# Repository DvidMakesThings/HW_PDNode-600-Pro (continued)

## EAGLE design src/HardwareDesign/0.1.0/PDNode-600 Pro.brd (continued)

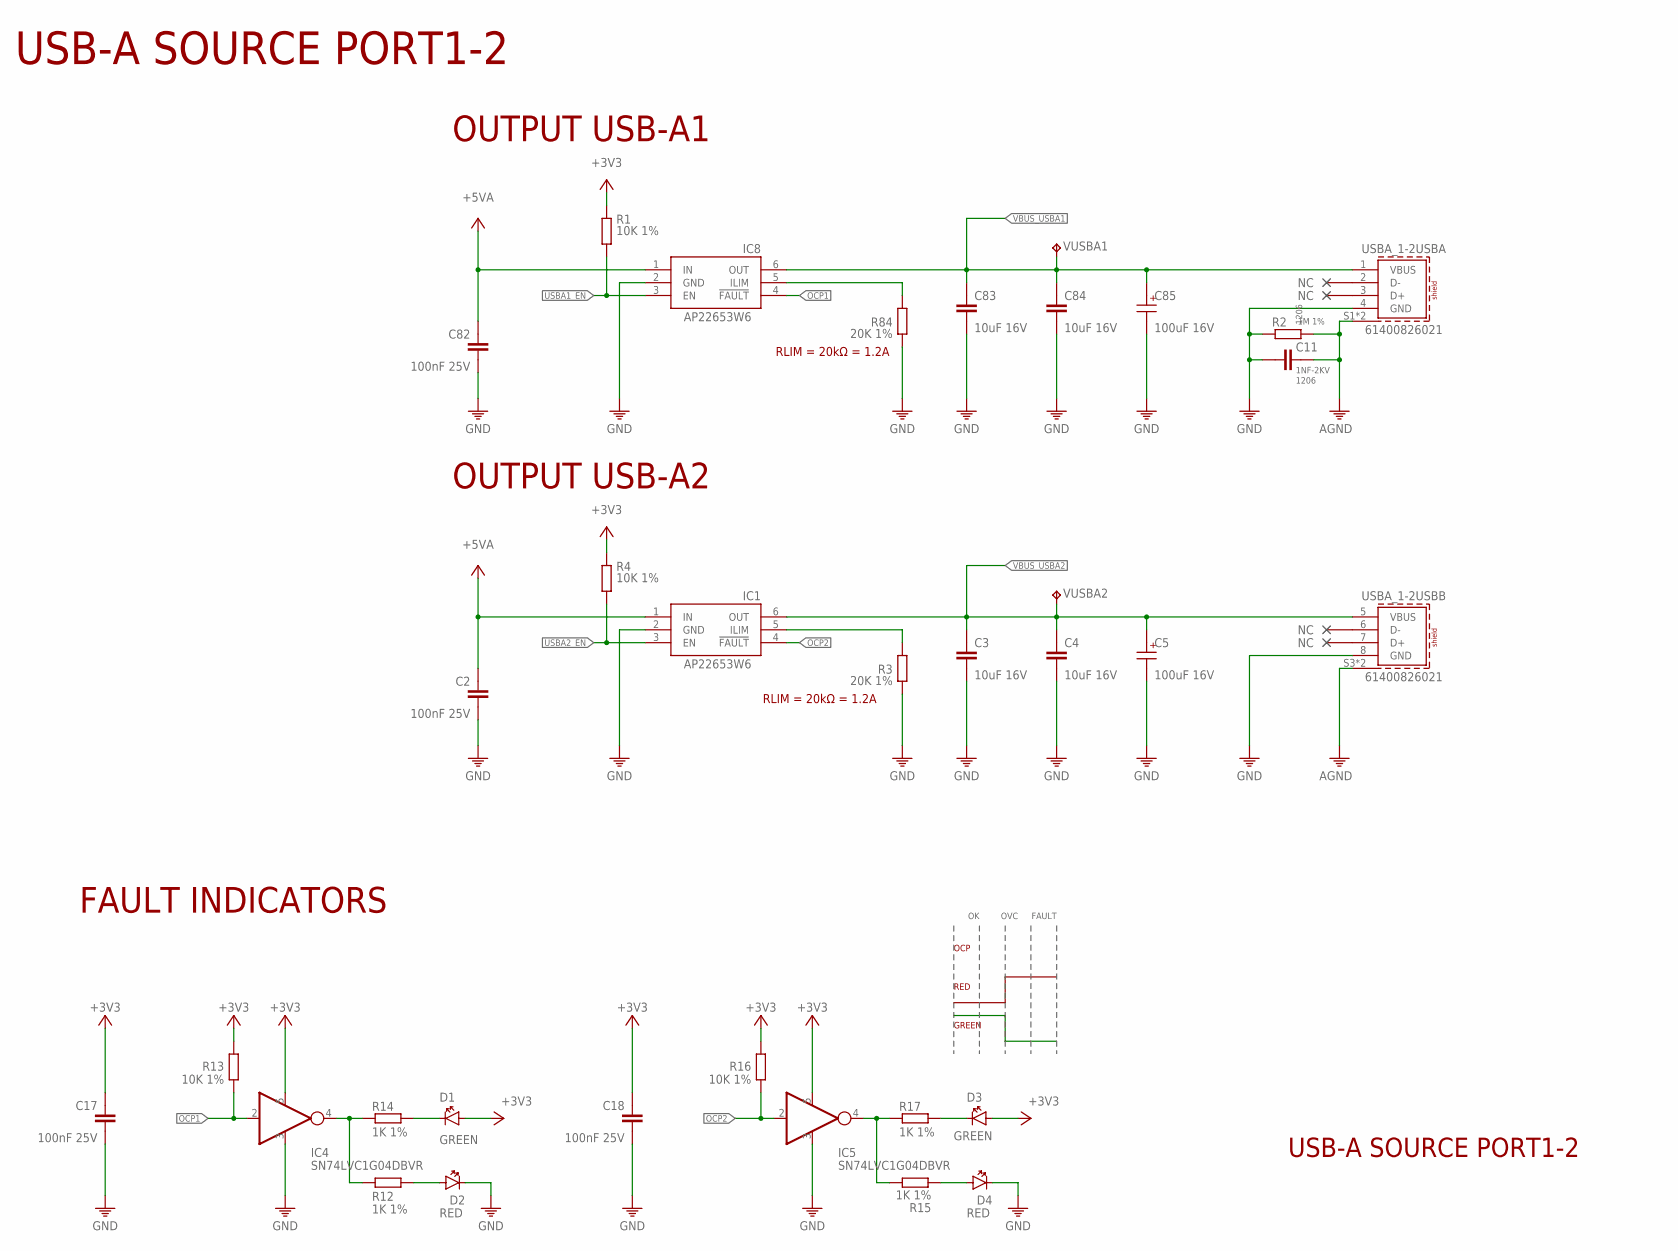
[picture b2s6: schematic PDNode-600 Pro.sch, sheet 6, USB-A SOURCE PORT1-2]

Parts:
C2, C17, C18, C82: 100nF 25V; 0201
C3, C4, C83, C84: 10uF 16V; 0603
C5, C85: 100uF 16V; 5X5.5(DXL)
C11: 1NF-2KV; 1206
D1, D3: GREEN; LEDC1608X35N_FLAT-G
D2, D4: RED; LEDC1608X35N_FLAT-R
IC1, IC8: AP22653W6; SOT23-6
IC4, IC5: SN74LVC1G04DBVR; SOT95P280X145-5N
R1, R4, R13, R16: 10K 1%; 0402
R2: 1M 1%; 1206
R3, R84: 20K 1%; 0201
R12, R14, R15, R17: 1K 1%; 0402
USBA_1-2: 61400826021
VUSBA1, VUSBA2: TPB1,27; B1,27

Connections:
+3V3: C17.1, C18.1, D1.A, D3.A, IC4.5 (V+), IC5.5 (V+), R1.1, R4.1, R13.2, R16.2; also elsewhere on the board
+5VA: C2.1, C82.1, IC1.1 (IN), IC8.1 (IN); also elsewhere on the board
AGND: C11.1, R2.2, USBA_1-2.S1 (SHIELD), USBA_1-2.S2 (SHIELD), USBA_1-2.S3 (SHIELD), USBA_1-2.S4 (SHIELD); also elsewhere on the board
GND: C2.2, C3.2, C4.2, C5.2 (-), C11.2, C17.2, C18.2, C82.2, C83.2, C84.2, C85.2 (-), D2.C, D4.C, IC1.2 (GND), IC4.3 (V-), IC5.3 (V-), IC8.2 (GND), R2.1, R3.2, R84.2, USBA_1-2.4 (GND), USBA_1-2.8 (GND); also elsewhere on the board
unnamed: IC1.5 (ILIM), R3.1
unnamed: D2.A, R12.2
unnamed: IC4.4 (OUT), R12.1, R14.1
unnamed: D1.C, R14.2
unnamed: D4.A, R15.1
unnamed: IC5.4 (OUT), R15.2, R17.1
unnamed: D3.C, R17.2
unnamed: IC8.5 (ILIM), R84.1
OCP1: IC4.2 (IN), IC8.4 (!FAULT), R13.1; also elsewhere on the board
OCP2: IC1.4 (!FAULT), IC5.2 (IN), R16.1; also elsewhere on the board
USBA1_EN: IC8.3 (EN), R1.2; also elsewhere on the board
USBA2_EN: IC1.3 (EN), R4.2; also elsewhere on the board
VBUS_USBA1: C83.1, C84.1, C85.1 (+), IC8.6 (OUT), USBA_1-2.1 (VBUS), VUSBA1.TP
VBUS_USBA2: C3.1, C4.1, C5.1 (+), IC1.6 (OUT), USBA_1-2.5 (VBUS), VUSBA2.TP

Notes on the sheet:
OUTPUT USB-A1
RLIM = 20kΩ = 1.2A
OUTPUT USB-A2
FAULT INDICATORS
USB-A SOURCE PORT1-2
OCP
RED
GREEN
OVC
FAULT

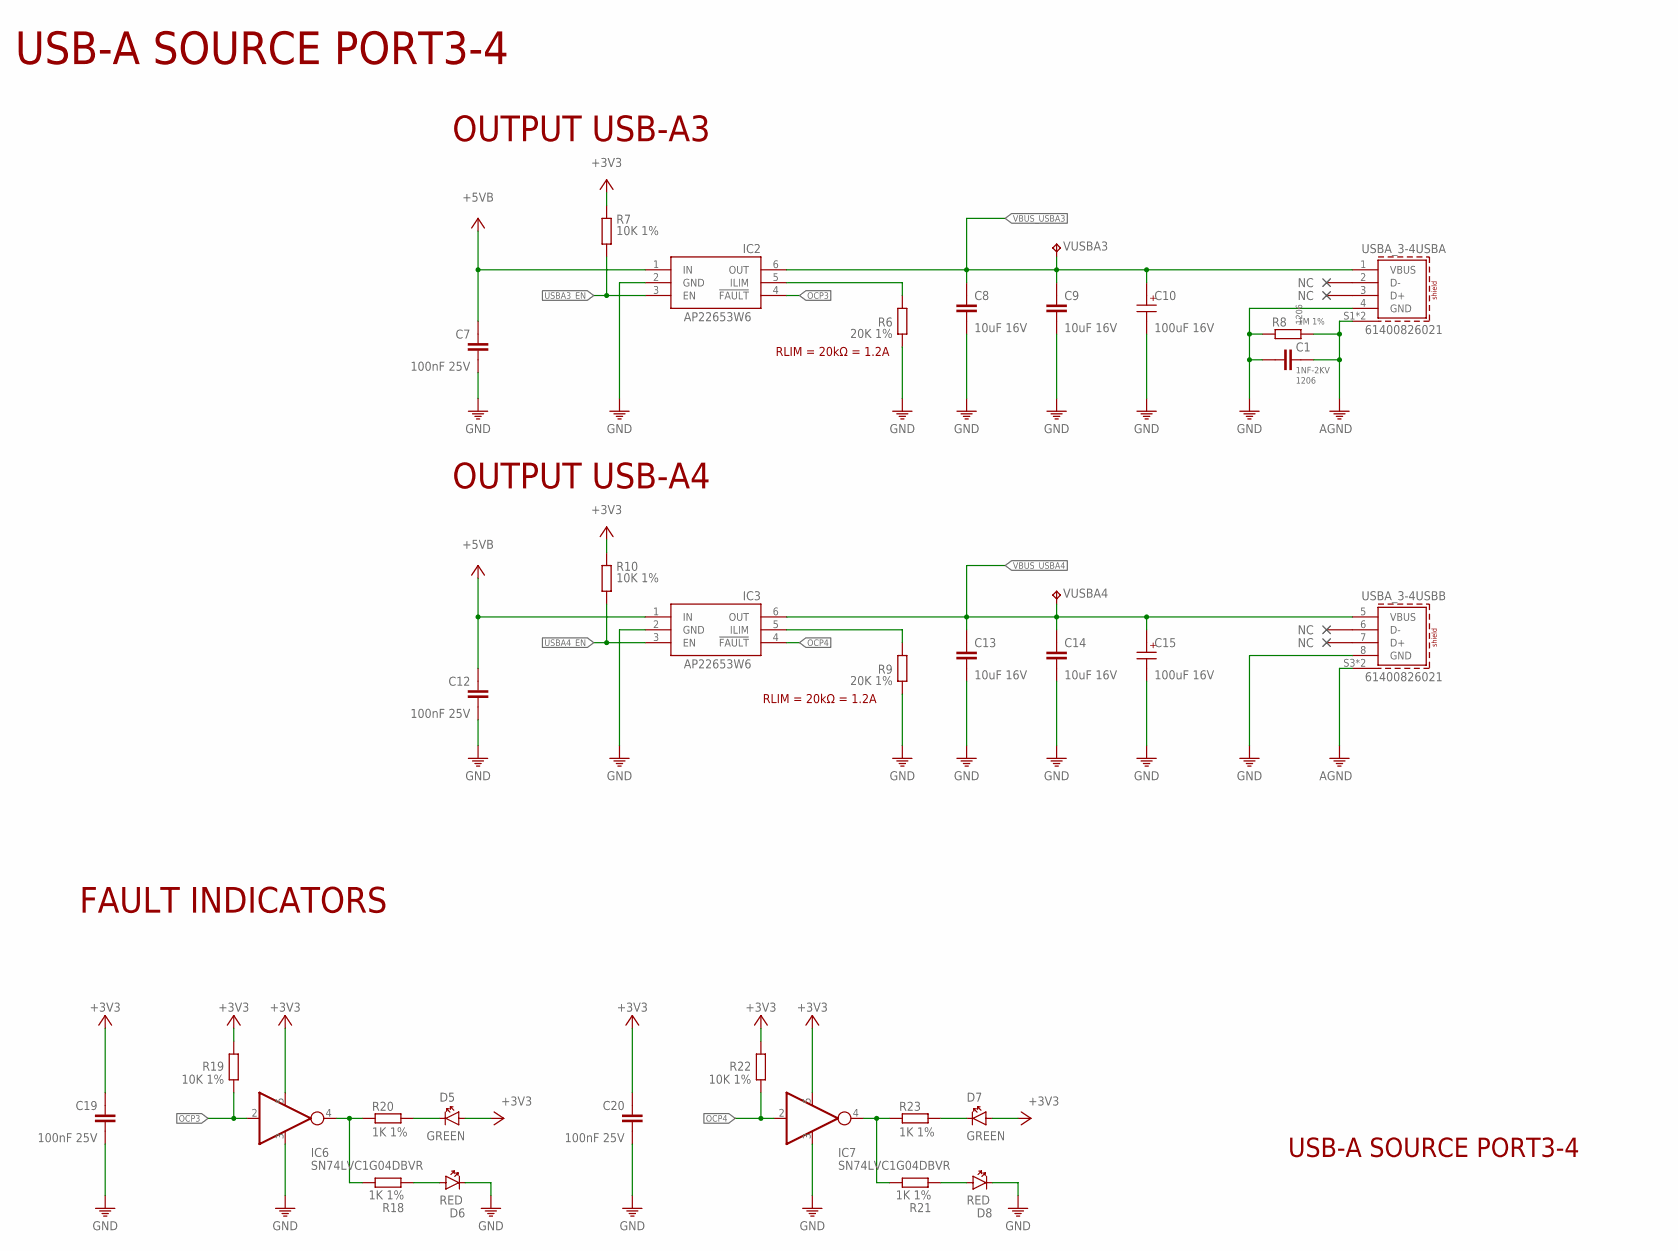
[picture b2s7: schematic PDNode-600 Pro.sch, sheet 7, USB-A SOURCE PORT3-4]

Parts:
C1: 1NF-2KV; 1206
C7, C12, C19, C20: 100nF 25V; 0201
C8, C9, C13, C14: 10uF 16V; 0603
C10, C15: 100uF 16V; 5X5.5(DXL)
D5, D7: GREEN; LEDC1608X35N_FLAT-G
D6, D8: RED; LEDC1608X35N_FLAT-R
IC2, IC3: AP22653W6; SOT23-6
IC6, IC7: SN74LVC1G04DBVR; SOT95P280X145-5N
R6, R9: 20K 1%; 0201
R7, R10, R19, R22: 10K 1%; 0402
R8: 1M 1%; 1206
R18, R20, R21, R23: 1K 1%; 0402
USBA_3-4: 61400826021
VUSBA3, VUSBA4: TPB1,27; B1,27

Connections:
+3V3: C19.1, C20.1, D5.A, D7.A, IC6.5 (V+), IC7.5 (V+), R7.1, R10.1, R19.2, R22.2; also elsewhere on the board
+5VB: C7.1, C12.1, IC2.1 (IN), IC3.1 (IN); also elsewhere on the board
AGND: C1.1, R8.2, USBA_3-4.S1 (SHIELD), USBA_3-4.S2 (SHIELD), USBA_3-4.S3 (SHIELD), USBA_3-4.S4 (SHIELD); also elsewhere on the board
GND: C1.2, C7.2, C8.2, C9.2, C10.2 (-), C12.2, C13.2, C14.2, C15.2 (-), C19.2, C20.2, D6.C, D8.C, IC2.2 (GND), IC3.2 (GND), IC6.3 (V-), IC7.3 (V-), R6.2, R8.1, R9.2, USBA_3-4.4 (GND), USBA_3-4.8 (GND); also elsewhere on the board
unnamed: IC2.5 (ILIM), R6.1
unnamed: IC3.5 (ILIM), R9.1
unnamed: D6.A, R18.1
unnamed: IC6.4 (OUT), R18.2, R20.1
unnamed: D5.C, R20.2
unnamed: D8.A, R21.1
unnamed: IC7.4 (OUT), R21.2, R23.1
unnamed: D7.C, R23.2
OCP3: IC2.4 (!FAULT), IC6.2 (IN), R19.1; also elsewhere on the board
OCP4: IC3.4 (!FAULT), IC7.2 (IN), R22.1; also elsewhere on the board
USBA3_EN: IC2.3 (EN), R7.2; also elsewhere on the board
USBA4_EN: IC3.3 (EN), R10.2; also elsewhere on the board
VBUS_USBA3: C8.1, C9.1, C10.1 (+), IC2.6 (OUT), USBA_3-4.1 (VBUS), VUSBA3.TP
VBUS_USBA4: C13.1, C14.1, C15.1 (+), IC3.6 (OUT), USBA_3-4.5 (VBUS), VUSBA4.TP

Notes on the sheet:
OUTPUT USB-A3
RLIM = 20kΩ = 1.2A
OUTPUT USB-A4
USB-A SOURCE PORT3-4
FAULT INDICATORS

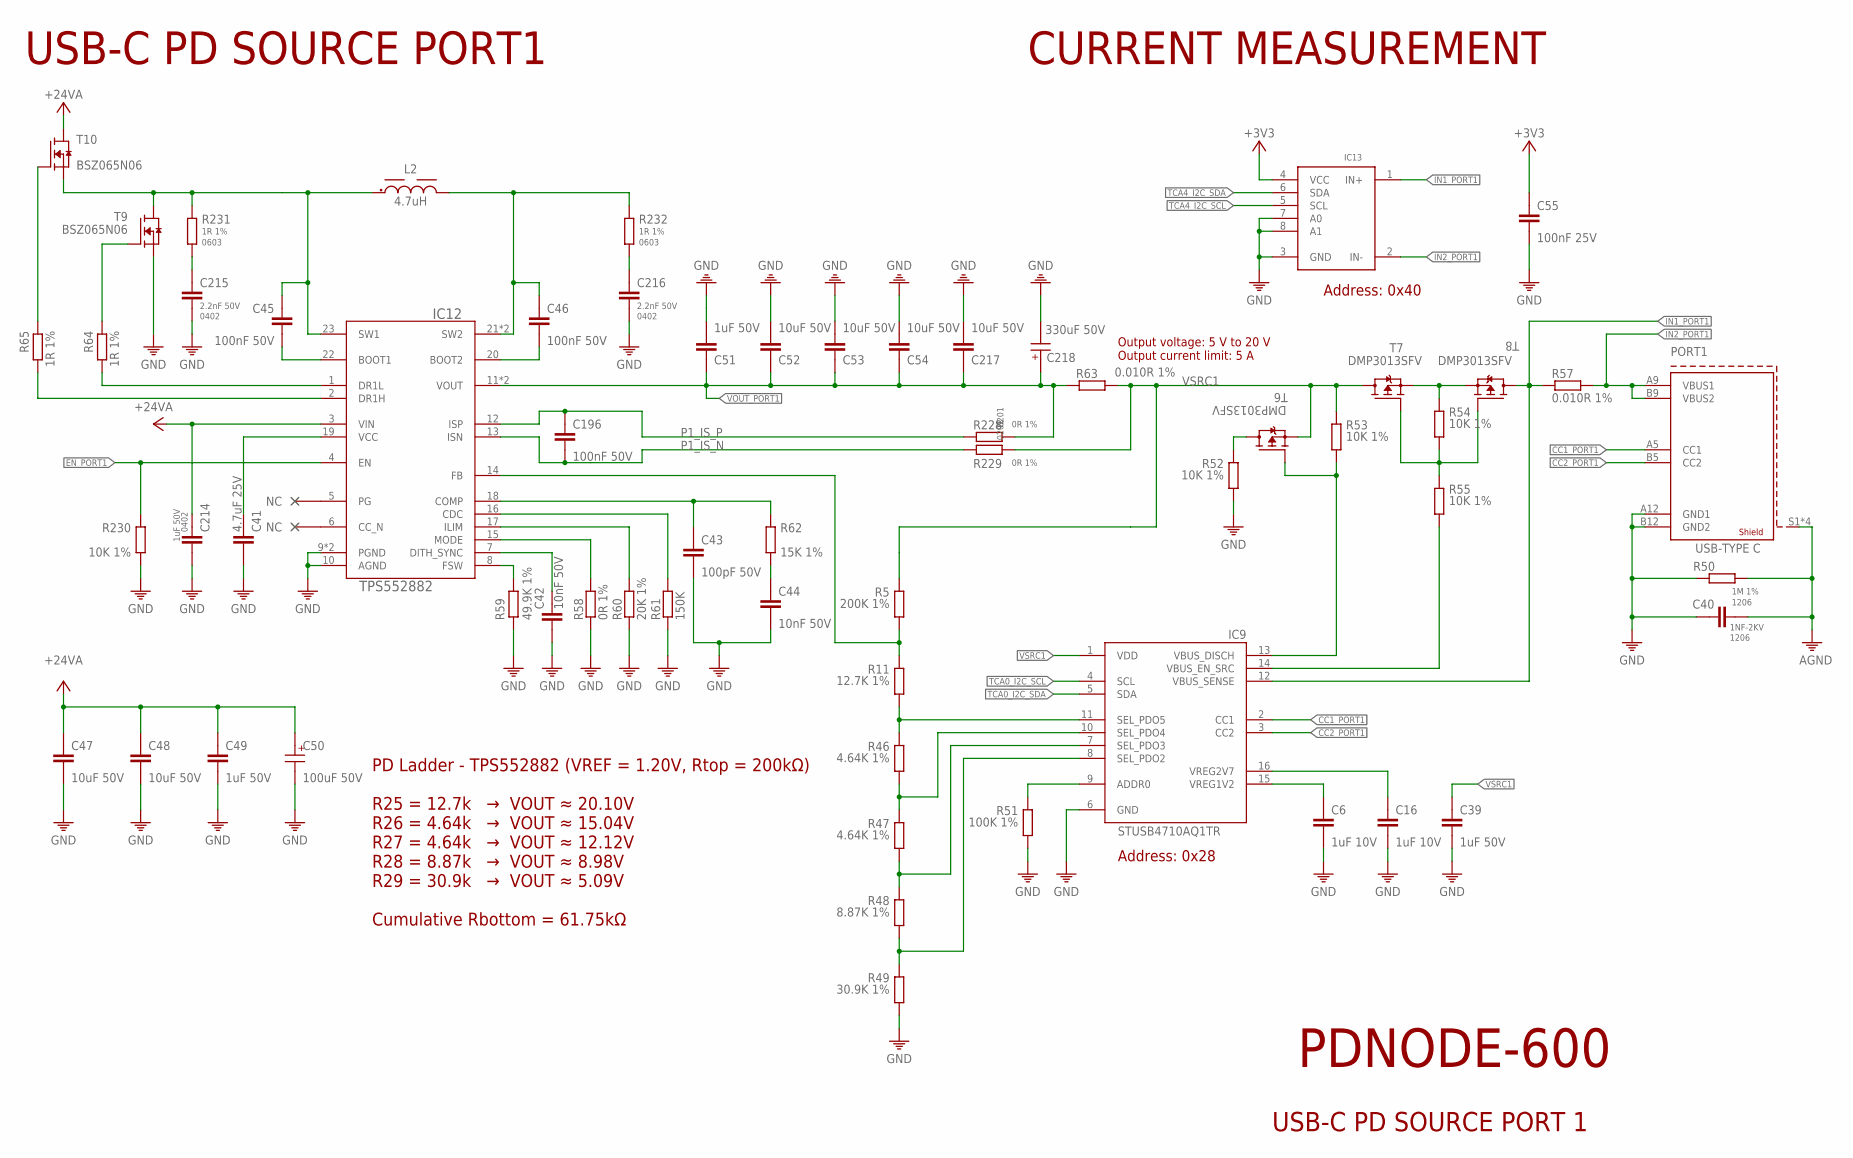
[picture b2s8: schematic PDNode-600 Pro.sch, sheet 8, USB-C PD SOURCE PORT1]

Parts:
C6, C16: 1uF 10V; 0201
C39: 1uF 50V; 0603
C40: 1NF-2KV; 1206
C41: 4.7uF 25V; 0402
C42, C44: 10nF 50V; 0201
C43: 100pF 50V; 0402
C45, C46, C196: 100nF 50V; 0402
C47, C48, C52, C53, C54, C217: 10uF 50V; 0805
C49: 1uF 50V; 0805
C50: 100uF 50V; 6.3X7.7(DXL)
C51, C214: 1uF 50V; 0402
C55: 100nF 25V; 0201
C215, C216: 2.2nF 50V; 0402
C218: 330uF 50V; 10X10.5(DXL)
IC9: STUSB4710AQ1TR; QFN50P300X300X55-16N
IC12: TPS552882; RPM0026A-MFG
IC13: INA219BIDCNT; SOT23-8
L2: 4.7uH; WE-PD_1280
PORT1: 632722100213
R5: 200K 1%; 0201
R11: 12.7K 1%; 0201
R46, R47: 4.64K 1%; 0201
R48: 8.87K 1%; 0201
R49: 30.9K 1%; 0201
R50: 1M 1%; 1206
R51: 100K 1%; 0201
R52, R53, R55: 10K 1%; 0402
R54, R230: 10K 1%; 0201
R57, R63: 0.010R 1%; 2512
R58, R228, R229: 0R 1%; 0201
R59: 49.9K 1%; 0201
R60: 20K 1%; 0201
R61: 150K; R0201
R62: 15K 1%; 0201
R64, R65: 1R 1%; 0402
R231, R232: 1R 1%; 0603
T6, T7, T8: DMP3013SFV; POWERDI3333-8_UX_DIO-L
T9, T10: BSZ065N06; POWERDI3333-8_UX_DIO-L

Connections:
+3V3: C55.1, IC13.4 (VCC); also elsewhere on the board
+24V_A: C47.1, C48.1, C49.1, C50.1 (+), C214.1, IC12.3 (VIN), T10.5 (D), T10.6 (D), T10.7 (D), T10.8 (D), T10.9 (D); also elsewhere on the board
AGND: C40.2, PORT1.S1 (SHIELD1), PORT1.S2 (SHIELD1), PORT1.S3 (SHIELD1), PORT1.S4 (SHIELD1), R50.2; also elsewhere on the board
CC1_PORT1: IC9.2 (CC1), PORT1.A5 (CC1)
CC2_PORT1: IC9.3 (CC2), PORT1.B5 (CC2)
EN_PORT1: IC12.4 (EN), R230.1; also elsewhere on the board
GND: C6.2, C16.2, C39.2, C40.1, C41.2, C42.2, C43.2, C44.2, C47.2, C48.2, C49.2, C50.2 (-), C51.2, C52.2, C53.2, C54.2, C55.2, C214.2, C215.2, C216.2, C217.2, C218.2 (-), IC9.6 (GND), IC12.9 (PGND), IC12.10 (AGND), IC12.24 (PGND), IC13.3 (GND), IC13.7 (A0), IC13.8 (A1), PORT1.A12 (GND1), PORT1.B12 (GND2), R49.2, R50.1, R51.2, R52.2, R58.2, R59.2, R60.2, R61.2, R230.2, T9.1 (S), T9.2 (S), T9.3 (S); also elsewhere on the board
IN1_PORT1: IC9.12 (VBUS_SENSE), IC13.1 (IN+), R57.1, T8.5 (D), T8.6 (D), T8.7 (D), T8.8 (D), T8.9 (D)
IN2_PORT1: IC13.2 (IN-), PORT1.A9 (VBUS1), PORT1.B9 (VBUS2), R57.2
unnamed: IC12.14 (FB), R5.2, R11.1
unnamed: C215.1, R231.2
unnamed: C216.1, R232.2
unnamed: IC9.11 (SEL_PDO5), R11.2, R46.1
unnamed: IC9.10 (SEL_PDO4), R46.2, R47.1
unnamed: IC9.7 (SEL_PDO3), R47.2, R48.1
unnamed: IC9.8 (SEL_PDO2), R48.2, R49.1
unnamed: C6.1, IC9.15 (VREG1V2)
unnamed: C16.1, IC9.16 (VREG2V7)
unnamed: IC9.9 (ADDR0), R51.1
unnamed: R52.1, T6.5 (D), T6.6 (D), T6.7 (D), T6.8 (D), T6.9 (D)
unnamed: IC9.13 (VBUS_DISCH), R53.2, T6.4 (G)
unnamed: R54.1, T7.1 (S), T7.2 (S), T7.3 (S), T8.1 (S), T8.2 (S), T8.3 (S)
unnamed: R54.2, R55.1, T7.4 (G), T8.4 (G)
unnamed: IC9.14 (VBUS_EN_SRC), R55.2
unnamed: C44.1, R62.2
unnamed: IC12.8 (FSW), R59.1
unnamed: C42.1, IC12.7 (DITH_SYNC)
unnamed: IC12.15 (MODE), R58.1
unnamed: IC12.17 (ILIM), R60.1
unnamed: IC12.16 (CDC), R61.1
unnamed: C43.1, IC12.18 (COMP), R62.1
unnamed: C41.1, IC12.19 (VCC)
unnamed: C45.1, IC12.23 (SW1), L2.1, R231.1, T9.5 (D), T9.6 (D), T9.7 (D), T9.8 (D), T9.9 (D), T10.1 (S), T10.2 (S), T10.3 (S)
unnamed: C46.1, IC12.21 (SW2), IC12.25 (SW2), L2.2, R232.1
unnamed: C45.2, IC12.22 (BOOT1)
unnamed: C46.2, IC12.20 (BOOT2)
unnamed: R65.2, T10.4 (G)
unnamed: R64.2, T9.4 (G)
unnamed: IC12.1 (DR1L), R64.1
unnamed: IC12.2 (DR1H), R65.1
P1_IS_N: C196.2, IC12.13 (ISN), R229.1
P1_IS_P: C196.1, IC12.12 (ISP), R228.1
TCA0_I2C_SCL: IC9.4 (SCL); also elsewhere on the board
TCA0_I2C_SDA: IC9.5 (SDA); also elsewhere on the board
TCA4_I2C_SCL: IC13.5 (SCL); also elsewhere on the board
TCA4_I2C_SDA: IC13.6 (SDA); also elsewhere on the board
VOUT_PORT1: C51.1, C52.1, C53.1, C54.1, C217.1, C218.1 (+), IC12.11 (VOUT), IC12.26 (VOUT), R63.1, R228.2
VSRC1: C39.1, IC9.1 (VDD), R5.1, R53.1, R63.2, R229.2, T6.1 (S), T6.2 (S), T6.3 (S), T7.5 (D), T7.6 (D), T7.7 (D), T7.8 (D), T7.9 (D)

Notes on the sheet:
USB-C PD SOURCE PORT1
CURRENT MEASUREMENT
Output voltage: 5 V to 20 V Output current limit: 5 A
PD Ladder - TPS552882 (VREF = 1.20V, Rtop = 200kΩ) R25 = 12.7k → VOUT ≈ 20.10V R26 = 4.64k → VOUT ≈ 15.04V R27 = 4.64k → VOUT ≈ 12.12V R28 = 8.87k → VOUT ≈ 8.98V R29 = 30.9k → VOUT ≈ 5.09V Cumulative Rbottom = 61.75kΩ
Address: 0x40
Address: 0x28
USB-C PD SOURCE PORT 1
PDNODE-600

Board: 4 copper layers, 285 parts (8 on the bottom side), 167 nets, no tracks yet.

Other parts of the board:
U$1: ROHS_LOGO_0.18_IN
U$2: OSHW-LOGO-L

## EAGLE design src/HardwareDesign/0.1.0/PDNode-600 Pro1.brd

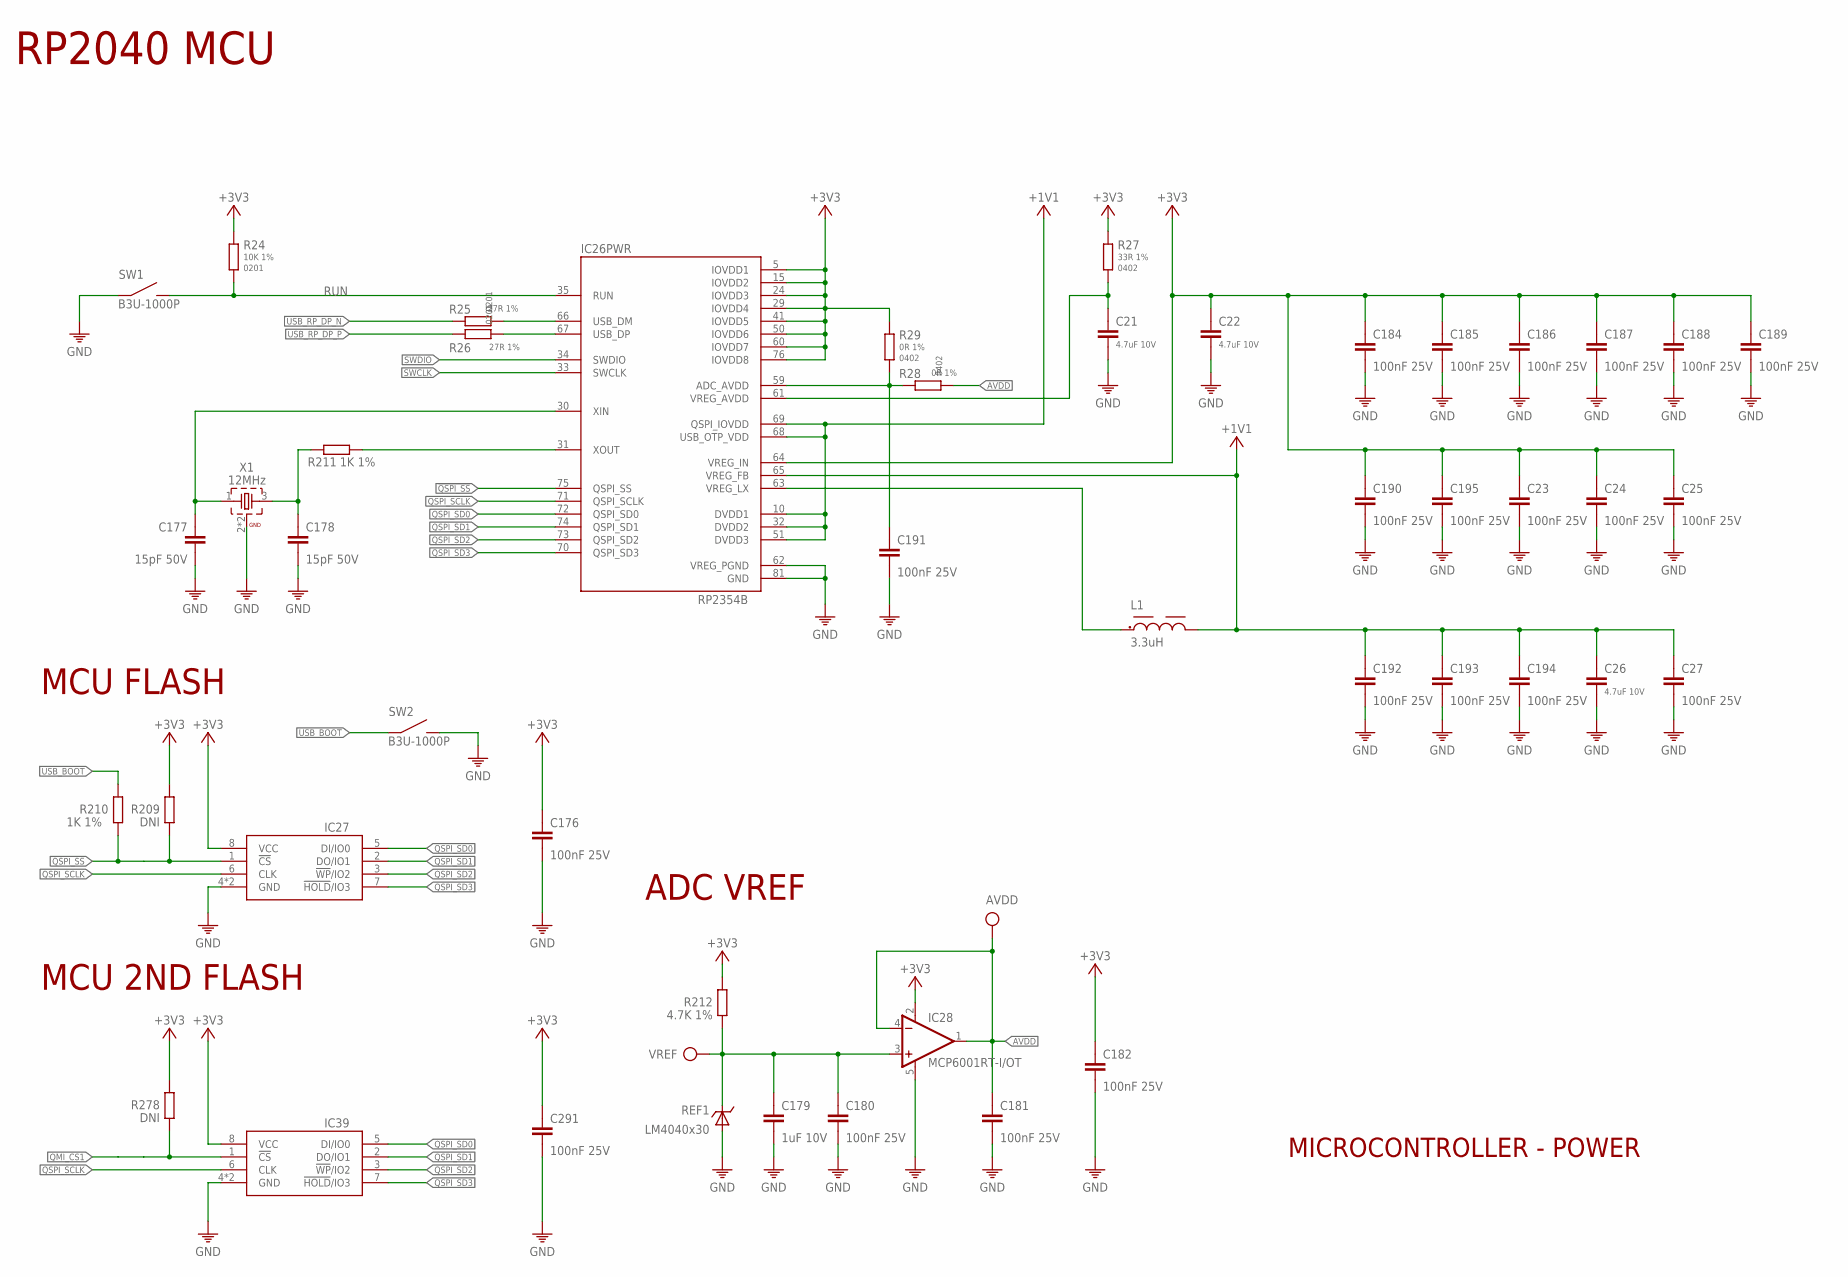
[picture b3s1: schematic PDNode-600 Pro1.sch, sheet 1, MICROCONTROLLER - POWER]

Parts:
AVDD: DNI; TP-ROUND
C21, C22, C26: 4.7uF 10V; 0402
C23, C24, C25, C27, C176, C180, C182, C184, C185, C186, C187, C188, C189, C190, C191, C192, C193, C194, C195, C291: 100nF 25V; 0201
C177, C178: 15pF 50V; 0201
C179: 1uF 10V; 0201
C181: 100nF 25V; 0402
IC26: RP2354B; QFN80-10X10
IC27, IC39: W25Q128JVPIQ; SON127P600X500X75-8N
IC28: MCP6001RT-I/OT; SOT23-5
L1: 3.3uH; 0805
R24: 10K 1%; 0201
R25, R26: 27R 1%; 0201
R27: 33R 1%; 0402
R28, R29: 0R 1%; 0402
R209, R278: DNI; R0201
R210, R211: 1K 1%; 0201
R212: 4.7K 1%; 0201
REF1: LM4040x30; SOT23
SW1, SW2: B3U-1000P
VREF: DNI; TP-ROUND
X1: 12MHz; WE-XTAL_CFPX-180

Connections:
!QSPI_SS: IC26.75 (QSPI_SS), IC27.1 (!CS), R209.1, R210.2
+1V1: C26.1, C27.1, C192.1, C193.1, C194.1, IC26.10 (DVDD1), IC26.32 (DVDD2), IC26.51 (DVDD3), IC26.65 (VREG_FB), IC26.68 (USB_OTP_VDD), IC26.69 (QSPI_IOVDD), L1.2
+3V3: C22.1, C23.1, C24.1, C25.1, C176.1, C182.1, C184.1, C185.1, C186.1, C187.1, C188.1, C189.1, C190.1, C195.1, C291.1, IC26.5 (IOVDD1), IC26.15 (IOVDD2), IC26.24 (IOVDD3), IC26.29 (IOVDD4), IC26.41 (IOVDD5), IC26.50 (IOVDD6), IC26.60 (IOVDD7), IC26.64 (VREG_IN), IC26.76 (IOVDD8), IC27.8 (VCC), IC28.2 (V+), IC39.8 (VCC), R24.1, R27.1, R29.1, R209.2, R212.2, R278.2; also elsewhere on the board
ADC_AVDD: C191.1, IC26.59 (ADC_AVDD), R28.1, R29.2
AVDD: AVDD.TP, C181.1, IC28.1 (OUT), IC28.4 (-IN), R28.2
GND: C21.2, C22.2, C23.2, C24.2, C25.2, C26.2, C27.2, C176.2, C177.2, C178.2, C179.2, C180.2, C181.2, C182.2, C184.2, C185.2, C186.2, C187.2, C188.2, C189.2, C190.2, C191.2, C192.2, C193.2, C194.2, C195.2, C291.2, IC26.62 (VREG_PGND), IC26.81 (GND), IC27.4 (GND), IC27.PAD (GND), IC28.5 (V-), IC39.4 (GND), IC39.PAD (GND), REF1.2 (A), REF1.3 (A), SW1.1, SW2.2, X1.2 (GND), X1.4 (GND); also elsewhere on the board
unnamed: C21.1, IC26.61 (VREG_AVDD), R27.2
unnamed: IC26.63 (VREG_LX), L1.1
unnamed: C178.1, R211.1, X1.3 (2)
QMI_CS1: IC39.1 (!CS), R278.1; also elsewhere on the board
QSPI_SCLK: IC26.71 (QSPI_SCLK), IC27.6 (CLK), IC39.6 (CLK)
QSPI_SD0: IC26.72 (QSPI_SD0), IC27.5 (DI/IO0), IC39.5 (DI/IO0)
QSPI_SD1: IC26.74 (QSPI_SD1), IC27.2 (DO/IO1), IC39.2 (DO/IO1)
QSPI_SD2: IC26.73 (QSPI_SD2), IC27.3 (!WP!/IO2), IC39.3 (!WP!/IO2)
QSPI_SD3: IC26.70 (QSPI_SD3), IC27.7 (!HOLD!/IO3), IC39.7 (!HOLD!/IO3)
RP_XI: C177.1, IC26.30 (XIN), X1.1
RP_XO: IC26.31 (XOUT), R211.2
RUN: IC26.35 (RUN), R24.2, SW1.2; also elsewhere on the board
SWCLK: IC26.33 (SWCLK); also elsewhere on the board
SWDIO: IC26.34 (SWDIO); also elsewhere on the board
USB_BOOT: R210.1, SW2.1; also elsewhere on the board
USB_RPR_DP_N: IC26.66 (USB_DM), R25.2
USB_RPR_DP_P: IC26.67 (USB_DP), R26.2
USB_RP_DP_N: R25.1; also elsewhere on the board
USB_RP_DP_P: R26.1; also elsewhere on the board
VREF: C179.1, C180.1, IC28.3 (+IN), R212.1, REF1.1 (C), VREF.TP

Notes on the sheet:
RP2040 MCU
MCU FLASH
ADC VREF
MICROCONTROLLER - POWER
MCU 2ND FLASH

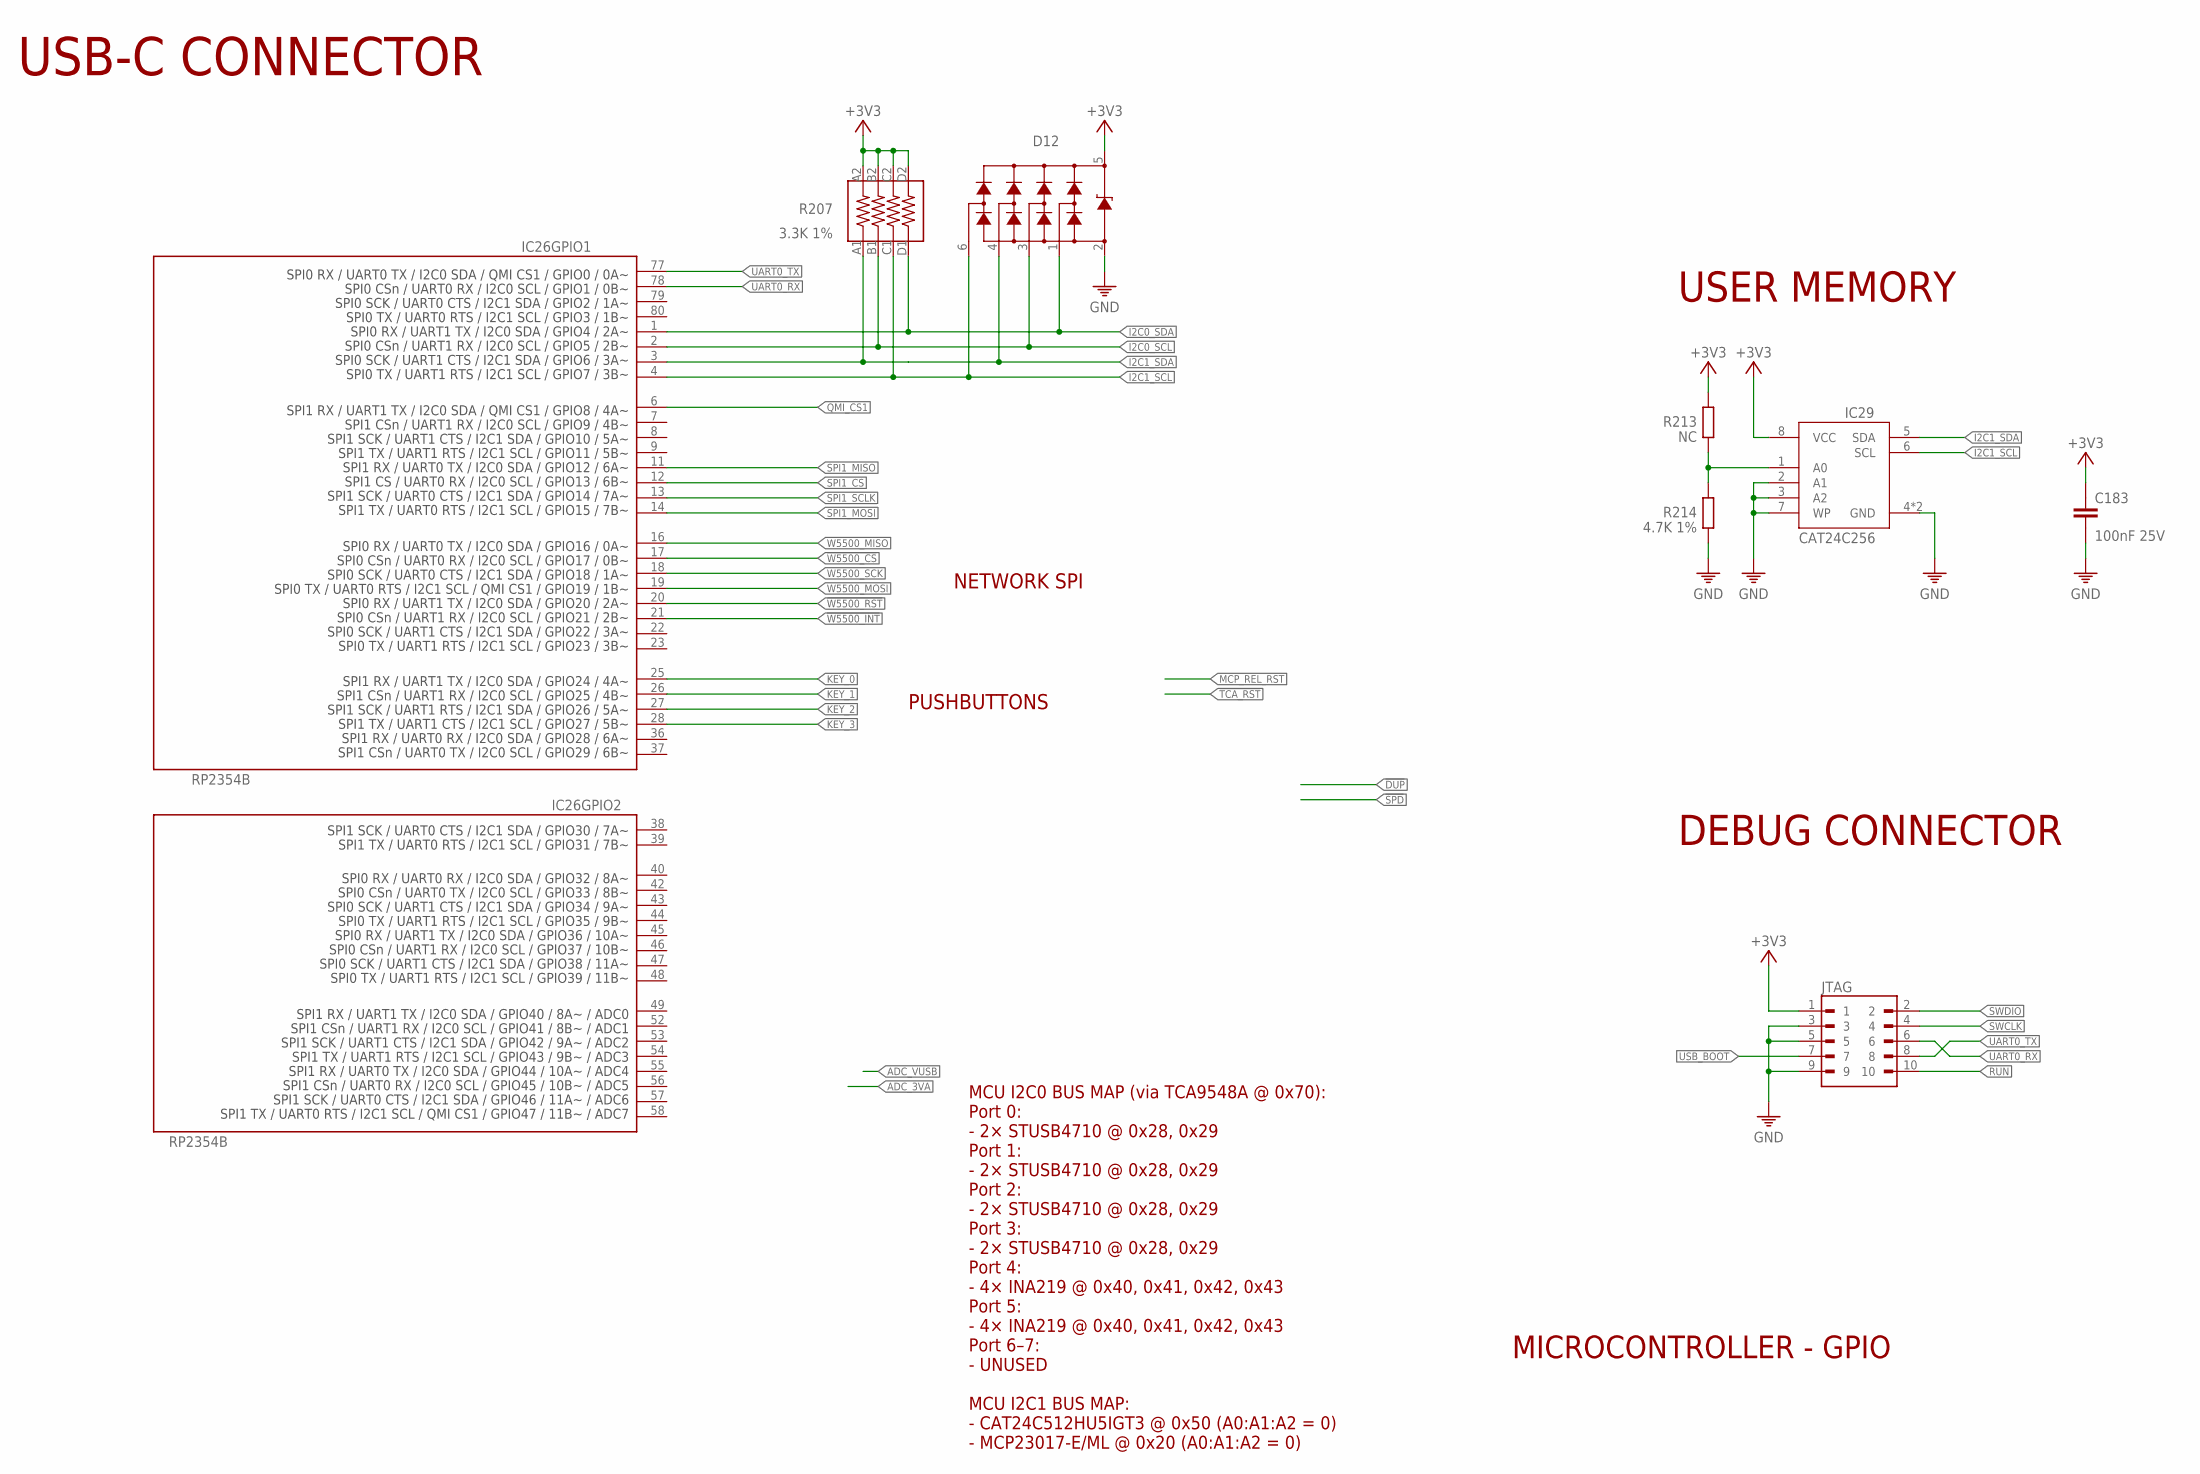
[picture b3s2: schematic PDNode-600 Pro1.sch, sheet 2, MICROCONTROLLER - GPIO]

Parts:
C183: 100nF 25V; 0201
D12: HDMIULC6-4SC6Y; SOT23-6
IC26: RP2354B; QFN80-10X10
IC29: CAT24C256HU4IGT3; SON50P300X200X50-9T130X140N
JTAG: 3220_10_0300_00
R207: 3.3K 1%; _0603X4-1206
R213: NC; R0201
R214: 4.7K 1%; 0201

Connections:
!W5500_CS: IC26.17 (GPIO17); also elsewhere on the board
!W5500_INT: IC26.21 (GPIO21); also elsewhere on the board
!W5500_RST: IC26.20 (GPIO20); also elsewhere on the board
+3V3: C183.1, D12.5, IC29.8 (VCC), JTAG.1, R207.A2 (8), R207.B2 (7), R207.C2 (6), R207.D2 (5), R213.2; also elsewhere on the board
GND: C183.2, D12.2, IC29.2 (A1), IC29.3 (A2), IC29.4 (GND), IC29.7 (WP), IC29.9 (GND), JTAG.3, JTAG.5, JTAG.9, R214.1; also elsewhere on the board
I2C0_SCL: D12.3, IC26.2 (GPIO5), R207.B1 (2); also elsewhere on the board
I2C0_SDA: D12.1, IC26.1 (GPIO4), R207.D1 (4); also elsewhere on the board
I2C1_SCL: D12.6, IC26.4 (GPIO7), IC29.6 (SCL), R207.C1 (3); also elsewhere on the board
I2C1_SDA: D12.4, IC26.3 (GPIO6), IC29.5 (SDA), R207.A1 (1); also elsewhere on the board
KEY_0: IC26.25 (GPIO24); also elsewhere on the board
KEY_1: IC26.26 (GPIO25); also elsewhere on the board
KEY_2: IC26.27 (GPIO26); also elsewhere on the board
KEY_3: IC26.28 (GPIO27); also elsewhere on the board
unnamed: IC29.1 (A0), R213.1, R214.2
QMI_CS1: IC26.6 (GPIO8); also elsewhere on the board
RUN: JTAG.10; also elsewhere on the board
SPI1_CS: IC26.12 (GPIO13)
SPI1_MISO: IC26.11 (GPIO12)
SPI1_MOSI: IC26.14 (GPIO15)
SPI1_SCLK: IC26.13 (GPIO14)
SWCLK: JTAG.4; also elsewhere on the board
SWDIO: JTAG.2; also elsewhere on the board
UART0_RX: IC26.78 (GPIO1), JTAG.6
UART0_TX: IC26.77 (GPIO0), JTAG.8
USB_BOOT: JTAG.7; also elsewhere on the board
W5500_MISO: IC26.16 (GPIO16); also elsewhere on the board
W5500_MOSI: IC26.19 (GPIO19); also elsewhere on the board
W5500_SCK: IC26.18 (GPIO18); also elsewhere on the board

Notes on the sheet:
USB-C CONNECTOR
NETWORK SPI
PUSHBUTTONS
MCU I2C0 BUS MAP (via TCA9548A @ 0x70): Port 0: - 2× STUSB4710 @ 0x28, 0x29 Port 1: - 2× STUSB4710 @ 0x28, 0x29 Port 2: - 2× STUSB4710 @ 0x28, 0x29 Port 3: - 2× STUSB4710 @ 0x28, 0x29 Port 4: - 4× INA219 @ 0x40, 0x41, 0x42, 0x43 Port 5: - 4× INA219 @ 0x40, 0x41, 0x42, 0x43 Port 6–7: - UNUSED MCU I2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
USER MEMORY
MICROCONTROLLER - GPIO
DEBUG CONNECTOR
